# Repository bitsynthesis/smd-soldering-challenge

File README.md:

# SMD Soldering Challenge

A soldering challenge PCB and blinking firmware written in assembly for
the ATTiny10.

Project created with [Kicad 5](http://www.kicad-pcb.org).

\
PCB

\
Front

\
Back

]\
Blinking [video](https://youtu.be/DWTuIyh-ze0)

# Programming

Requires avr-gcc, avrdude, and a TPI compatible programmer like the [Tiny
AVR Programmer](https://www.sparkfun.com/products/11801).

    make flash

# License

Copyright Ben Baker-Smith 2019.

This documentation describes Open Hardware and is licensed under the
[CERN OHL v.1.2](/LICENSE.TXT).

You may redistribute and modify this documentation under the terms of the
CERN OHL v.1.2. This documentation is distributed
WITHOUT ANY EXPRESS OR IMPLIED WARRANTY, INCLUDING OF
MERCHANTABILITY, SATISFACTORY QUALITY AND FITNESS FOR A
PARTICULAR PURPOSE. Please see the CERN OHL v.1.2 for applicable
conditions

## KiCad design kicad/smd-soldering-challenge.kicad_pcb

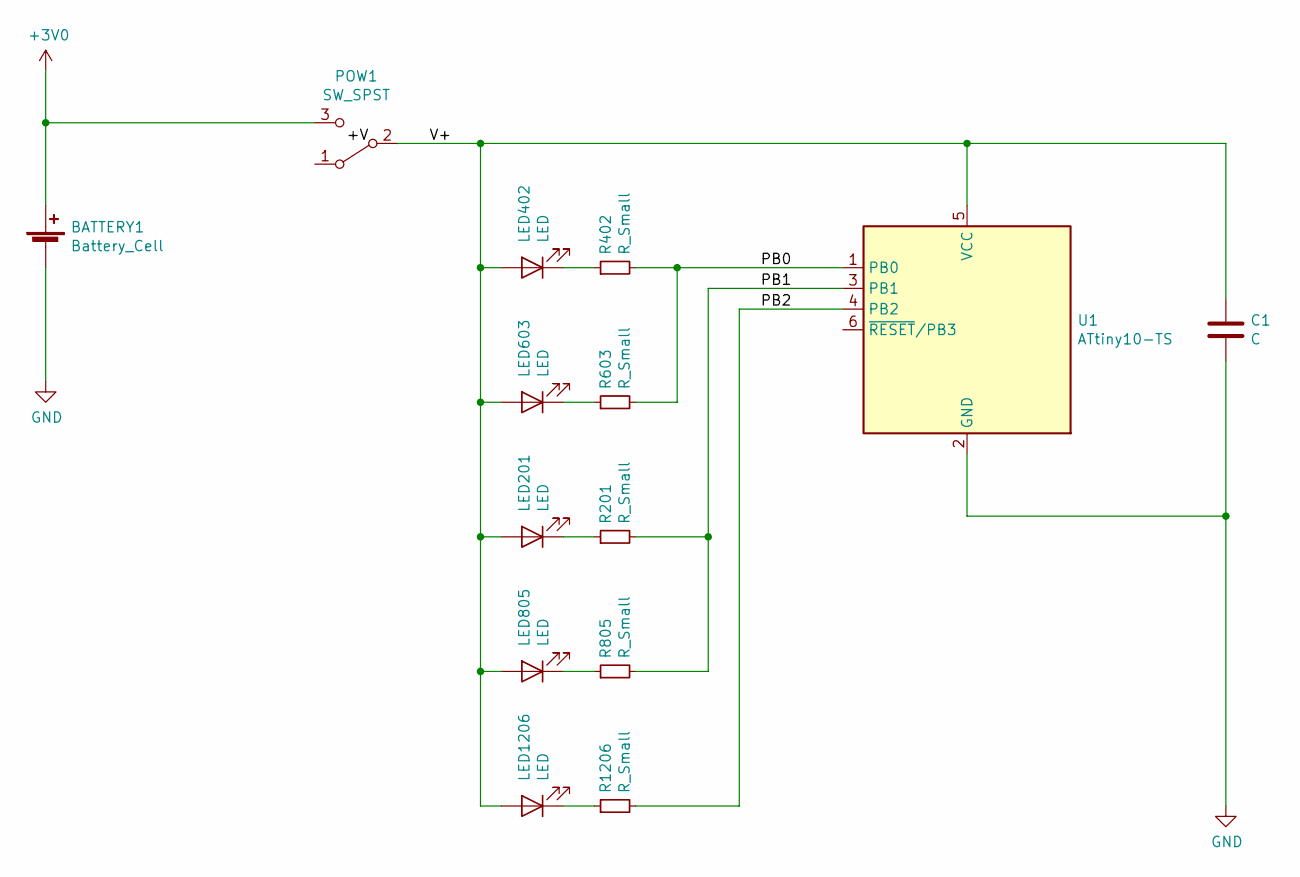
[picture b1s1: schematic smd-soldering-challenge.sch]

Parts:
BATTERY1: Battery_Cell; BatteryHolder12_5mm_cell_Harwin_S8201-46R_NoSilk
C1: C; C_0402_HandSoldering
LED201: LED; LED_0201_HandSoldering
LED402: LED; LED_0402_HandSoldering
LED603: LED; LED_0603_HandSoldering
LED805: LED; LED_0805_HandSoldering
LED1206: LED; LED_1206_HandSoldering
POW1: SW_SPST; SPDT_LowProfile_SMD_Switch_PCM12SMTR_NoSilk
R201: R_Small; R_0201_HandSoldering
R402: R_Small; R_0402_HandSoldering
R603: R_Small; R_0603_HandSoldering
R805: R_Small; R_0805_HandSoldering
R1206: R_Small; R_1206_HandSoldering
U1: ATtiny10-TS; SOT-23-6_Handsoldering

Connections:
+3V0: BATTERY1.1 (+), POW1.3 (C)
/PB0: R402.2, R603.2, U1.1 (PB0)
/PB1: R201.2, R805.2, U1.3 (PB1)
/PB2: R1206.2, U1.4 (PB2)
/V+: C1.1, LED201.2 (A), LED402.2 (A), LED603.2 (A), LED805.2 (A), LED1206.2 (A), POW1.2 (B), U1.5 (VCC)
GND: BATTERY1.2 (-), C1.2, U1.2 (GND)
unnamed: LED201.1 (K), R201.1
unnamed: LED402.1 (K), R402.1
unnamed: LED603.1 (K), R603.1
unnamed: LED805.1 (K), R805.1
unnamed: LED1206.1 (K), R1206.1

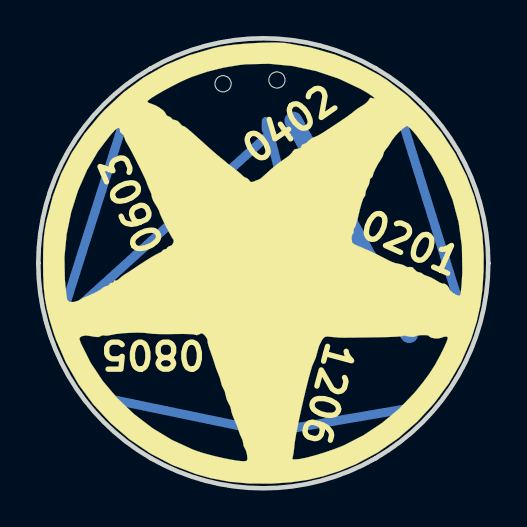
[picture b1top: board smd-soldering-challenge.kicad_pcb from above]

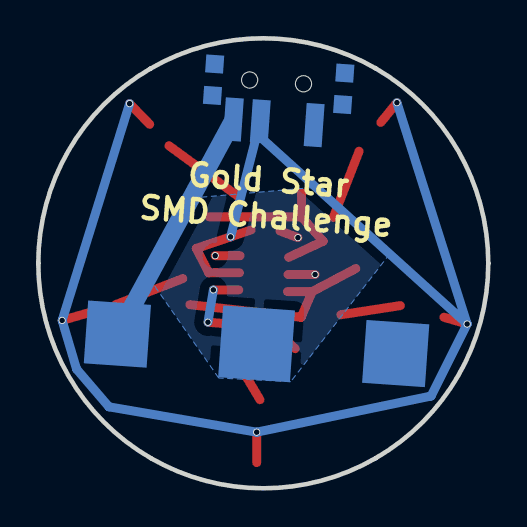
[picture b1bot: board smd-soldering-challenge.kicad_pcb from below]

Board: 2 copper layers, 25.0 x 25.0 mm, 14 parts (2 on the bottom side), 11 nets.

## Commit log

2019-10-03 Working program with attiny10 and tiny avr programmer
2019-10-03 Blinky
2019-10-04 Working assembly blinky
2019-10-04 Multiple patterns
2019-10-05 More patterns
2019-10-05 ASM patterns
2019-10-06 Assembly speed modulation
2019-10-06 More pattern work
2019-10-12 Fix speed change bug
2019-10-12 Slow speed change way down
2019-10-15 Add kicad resources
2019-10-18 Images for docs
2019-10-20 Prepare for release
    - Add CHANGELOG
    - Add README
    - Add License
    - Remove C PoC
    - Clean up Makefile
2019-10-20 ASM cleanup and documentation
2019-10-20 README
2019-10-20 Embed video in README
2019-10-20 Video in README
2019-10-20 Blinking gif
2019-10-21 Rename kicad files
2019-10-21 Finish commenting and renaming ASM
2019-10-21 Comment cleanup
2019-10-21 FAST and SLOW
